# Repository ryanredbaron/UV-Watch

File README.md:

# UV Watch
## Current MVP
- 10 hours of battery
- Track UV/% burned
- Close enough battery tracking
 
## Project List
1. [x] Clock refinement 
2. [x] Battery shut off
3. [x] Sunscreen apply
4. [ ] Sun reset
5. [x] Less sensitive to sun 
6. [?] Uv sensor voltage revamp
7. [x] Low power mode
8. [x] Input time from PC

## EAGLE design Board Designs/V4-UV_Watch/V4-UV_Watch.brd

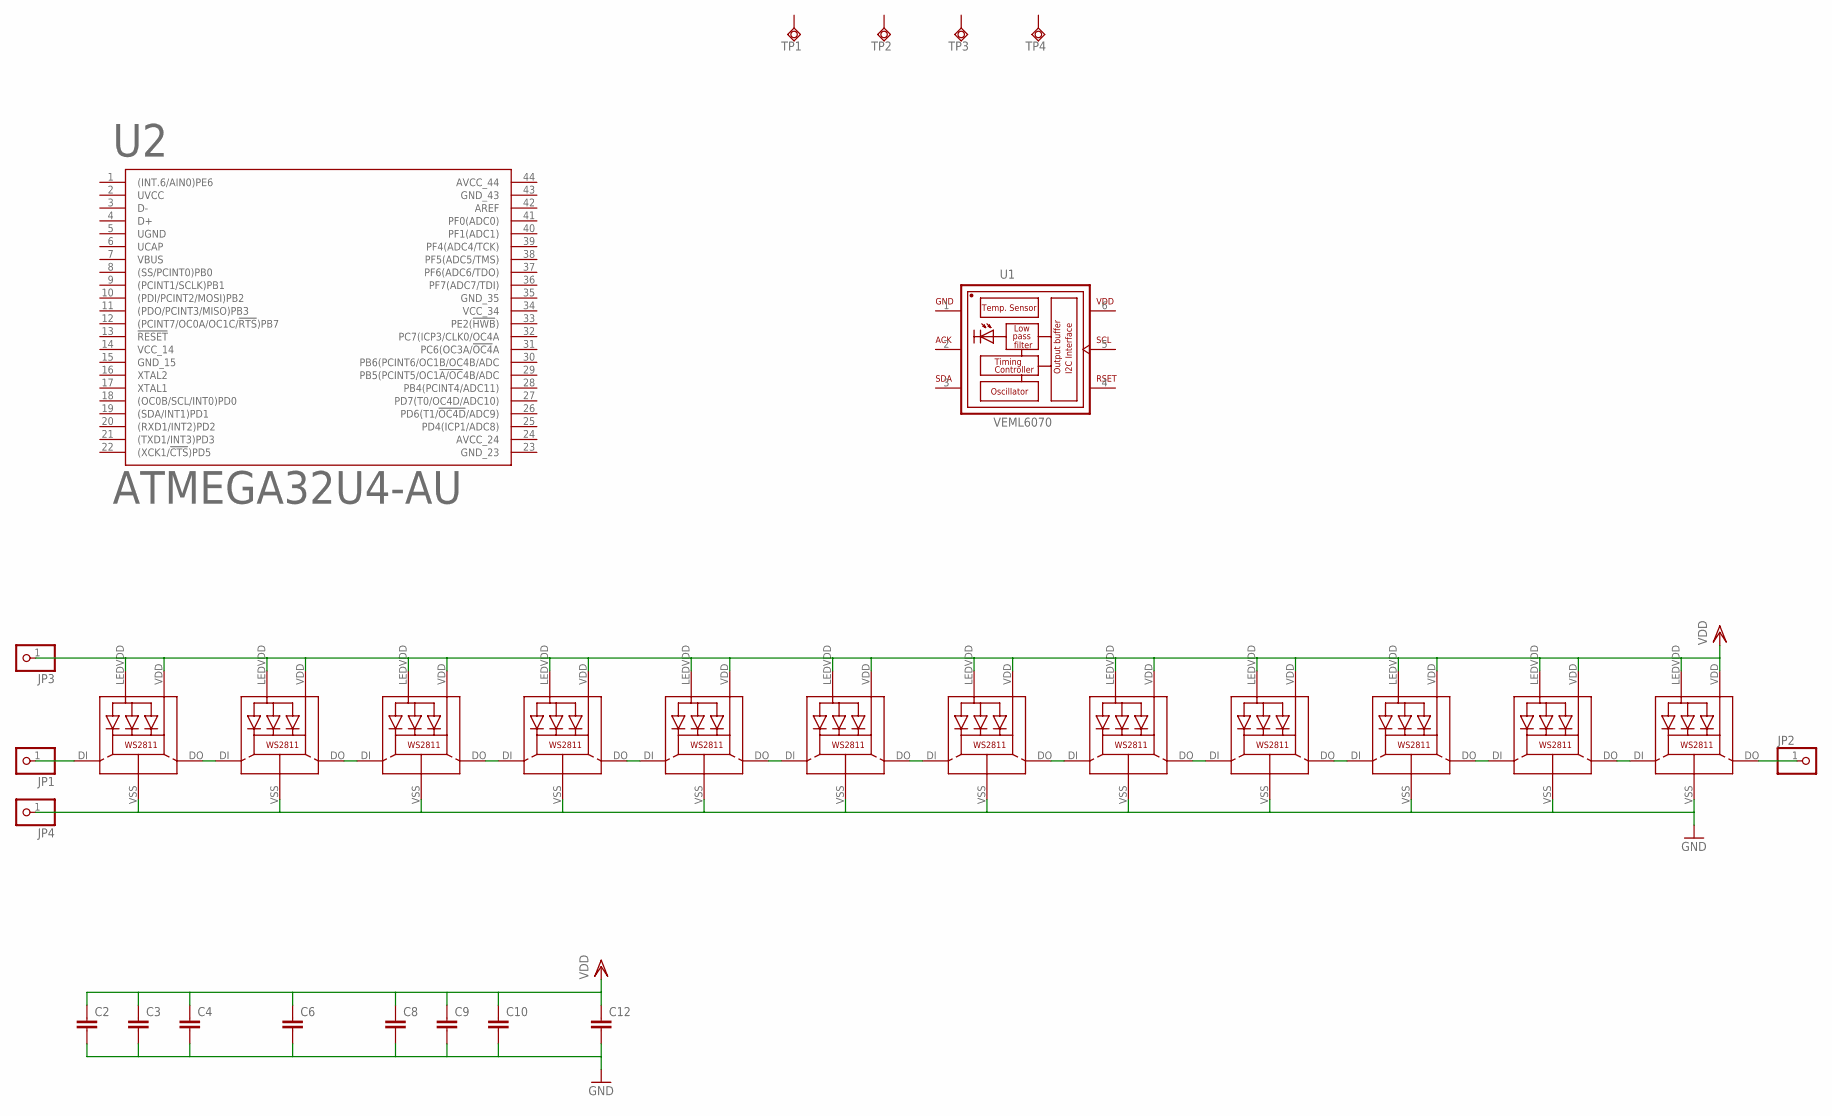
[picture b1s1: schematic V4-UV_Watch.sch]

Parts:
C2, C3, C4, C6, C8, C9, C10, C12: C-EUC0603; C0603
JP1, JP2, JP3, JP4: PINHD-1X1CB; 1X01-CLEANBIG
LED1, LED2, LED3, LED4, LED5, LED6, LED7, LED8, LED9, LED10, LED11, LED12: WS28115050
TP1, TP2, TP3, TP4: TESTPAD_TPSQTP20SQ; TESTPAD_TP20SQ
U1: VEML6070; PHODET_VEML6070
U2: ATMEGA32U4-AU; 44-TQFP

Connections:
AVCC_24: U2.24 (AVCC_24)
AVCC_44: U2.44 (AVCC_44)
GND: C2.2, C3.2, C4.2, C6.2, C8.2, C9.2, C10.2, C12.2, JP4.1, LED1.VSS (GND), LED2.VSS (GND), LED3.VSS (GND), LED4.VSS (GND), LED5.VSS (GND), LED6.VSS (GND), LED7.VSS (GND), LED8.VSS (GND), LED9.VSS (GND), LED10.VSS (GND), LED11.VSS (GND), LED12.VSS (GND), U1.1 (GND)
GND_15: U2.15 (GND_15)
GND_23: U2.23 (GND_23)
GND_35: U2.35 (GND_35)
GND_43: U2.43 (GND_43)
unnamed: LED1.DO, LED2.DI
unnamed: LED2.DO, LED3.DI
unnamed: LED3.DO, LED4.DI
unnamed: LED4.DO, LED5.DI
unnamed: LED5.DO, LED6.DI
unnamed: LED6.DO, LED7.DI
unnamed: LED7.DO, LED8.DI
unnamed: LED8.DO, LED9.DI
unnamed: LED9.DO, LED10.DI
unnamed: LED10.DO, LED11.DI
unnamed: LED11.DO, LED12.DI
unnamed: JP1.1, LED1.DI
unnamed: JP2.1, LED12.DO
UCAP: U2.6 (UCAP)
UGND: U2.5 (UGND)
UVCC: U2.2 (UVCC)
VCC_14: U2.14 (VCC_14)
VCC_34: U2.34 (VCC_34)
VDD: C2.1, C3.1, C4.1, C6.1, C8.1, C9.1, C10.1, C12.1, JP3.1, LED1.LEDVDD, LED1.VDD, LED2.LEDVDD, LED2.VDD, LED3.LEDVDD, LED3.VDD, LED4.LEDVDD, LED4.VDD, LED5.LEDVDD, LED5.VDD, LED6.LEDVDD, LED6.VDD, LED7.LEDVDD, LED7.VDD, LED8.LEDVDD, LED8.VDD, LED9.LEDVDD, LED9.VDD, LED10.LEDVDD, LED10.VDD, LED11.LEDVDD, LED11.VDD, LED12.LEDVDD, LED12.VDD, U1.6 (VDD)

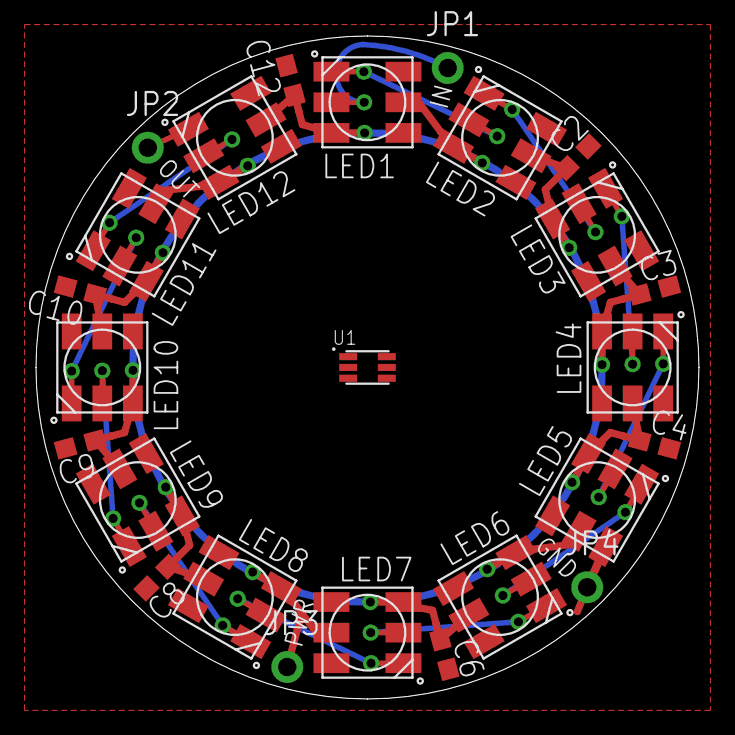
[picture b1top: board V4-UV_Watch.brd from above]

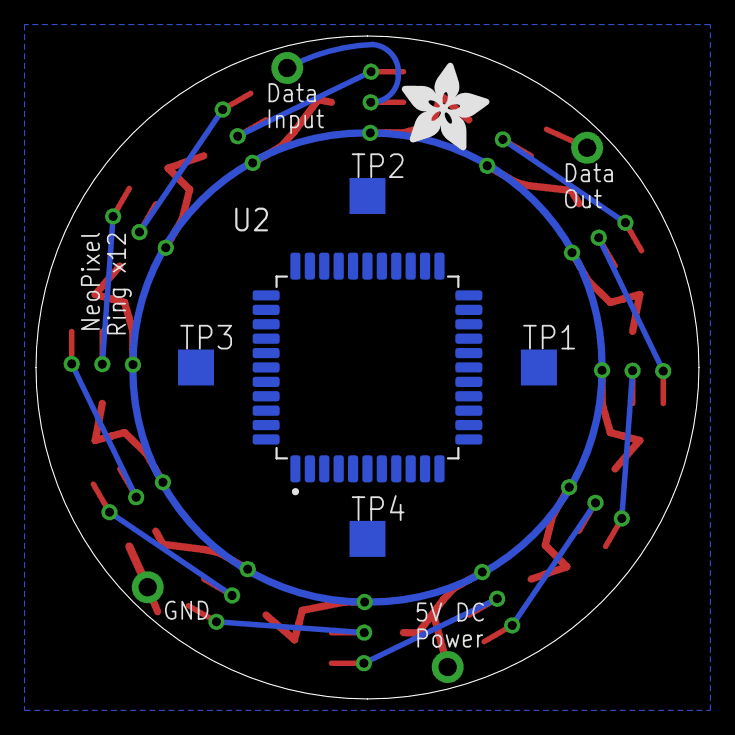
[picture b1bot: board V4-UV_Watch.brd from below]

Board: 2 copper layers, 36.8 x 36.8 mm, 33 parts (6 on the bottom side), 15 nets.

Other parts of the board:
U$1, U$2: GUIDE-STAR-12
U$3: ADAFRUIT_5MM

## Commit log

2019-08-12 Initial Load
2019-08-25 adding eagle files
2019-08-25 V4 hardware
2019-08-25 Moved files
2019-08-26 New board design
2022-09-28 changing to v2
2022-09-28 reading adjustments
2022-10-03 adding sunscreen
2022-10-21 Merging Mark's Firmware
2022-10-21 Updating code
2022-10-21 Combined old features
2022-11-01 Mocap testing
2022-11-10 voltage ref change
2022-11-15 Changing LED update method
2022-11-17 Added Alex's clock
2022-11-19 File structure update
2022-11-21 voltage cutoff, input from PC
2022-11-21 adding long presses
2022-11-21 Sunscreen reporting
2022-11-22 Latching UV
2023-03-06 time adjustments

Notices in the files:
parts and their libraries:
microbuilder: This work is placed in the public domain, and may be freely used for commercial and non-commercial work with the following conditions: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
